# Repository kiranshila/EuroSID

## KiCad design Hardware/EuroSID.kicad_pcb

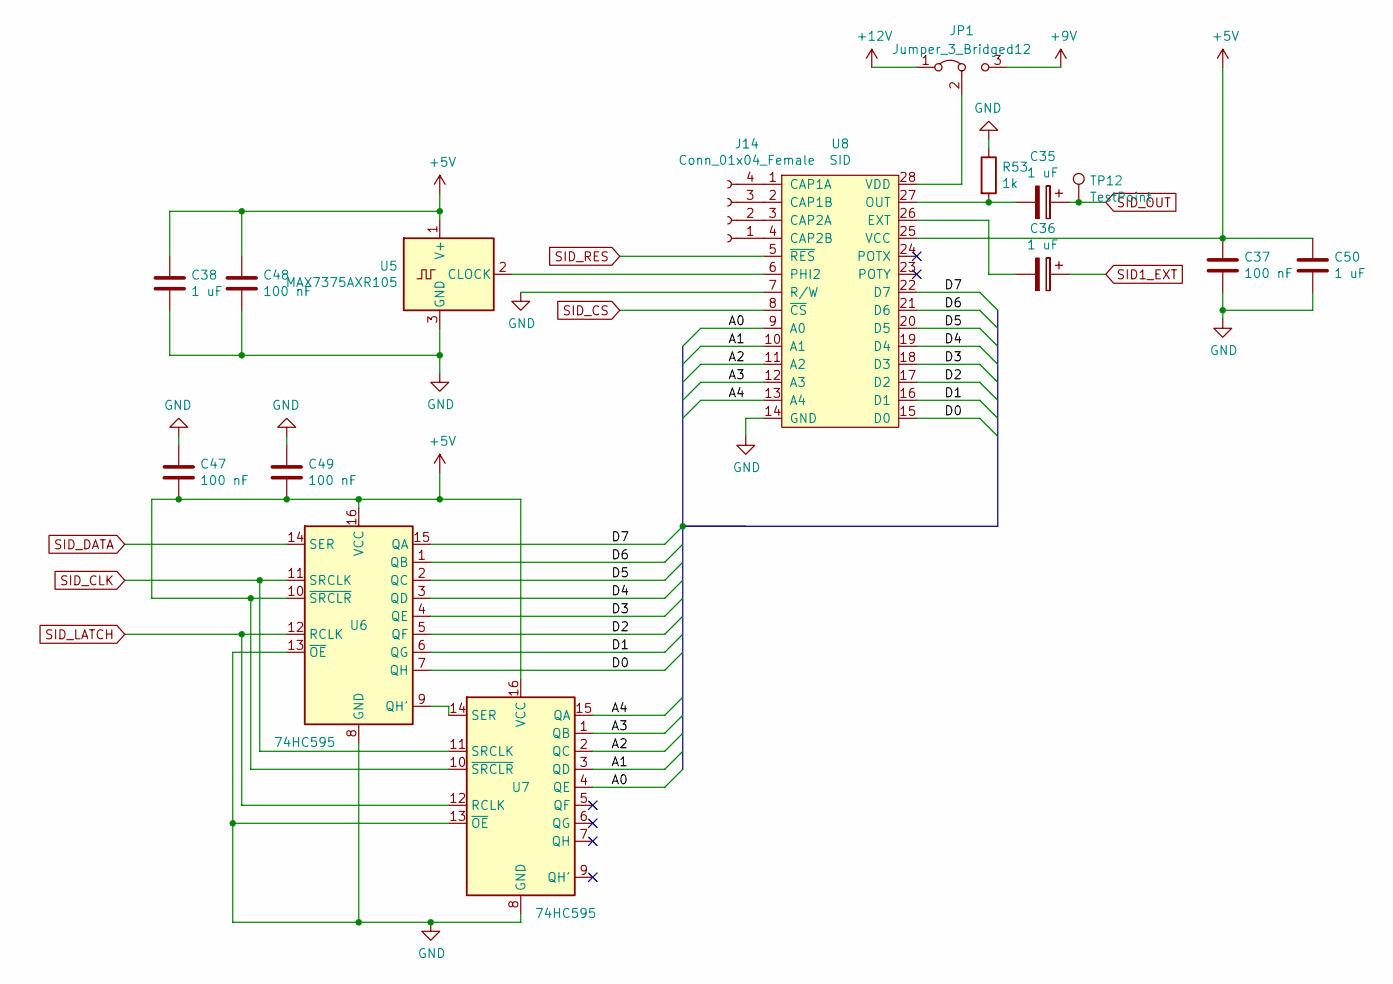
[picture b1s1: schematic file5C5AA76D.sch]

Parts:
C35, C36: 1 uF; CP_EIA-2012-12_Kemet-R
C37, C47, C48, C49: 100 nF; C_0603_1608Metric
C38, C50: 1 uF; C_0603_1608Metric
J14: Conn_01x04_Female; PinSocket_1x04_P2.54mm_Vertical
JP1: Jumper_3_Bridged12; PinHeader_1x03_P2.54mm_Vertical_SMD_Pin1Left
R53: 1k; R_0603_1608Metric
TP12: TestPoint; TestPoint_Pad_D1.0mm
U5: MAX7375AXR105; SOT-323_SC-70
U6, U7: 74HC595; SOIC-16_3.9x9.9mm_P1.27mm
U8: SID; DIP-28_W16.51mm_SMDSocket_LongPads

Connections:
+9V: JP1.3 (B); also elsewhere on the board
+12V: JP1.1 (A); also elsewhere on the board
/SID Chip/A0: U7.4 (QE), U8.9 (A0)
/SID Chip/A1: U7.3 (QD), U8.10 (A1)
/SID Chip/A2: U7.2 (QC), U8.11 (A2)
/SID Chip/A3: U7.1 (QB), U8.12 (A3)
/SID Chip/A4: U7.15 (QA), U8.13 (A4)
/SID Chip/D0: U6.7 (QH), U8.15 (D0)
/SID Chip/D1: U6.6 (QG), U8.16 (D1)
/SID Chip/D2: U6.5 (QF), U8.17 (D2)
/SID Chip/D3: U6.4 (QE), U8.18 (D3)
/SID Chip/D4: U6.3 (QD), U8.19 (D4)
/SID Chip/D5: U6.2 (QC), U8.20 (D5)
/SID Chip/D6: U6.1 (QB), U8.21 (D6)
/SID Chip/D7: U6.15 (QA), U8.22 (D7)
GND: C37.2, C38.2, C47.1, C48.2, C49.1, C50.2, R53.1, U5.3 (GND), U6.8 (GND), U6.13 (~OE), U7.8 (GND), U7.13 (~OE), U8.7 (R/W), U8.14 (GND); also elsewhere on the board
unnamed: C35.2, R53.2, U8.27 (OUT)
unnamed: C36.2, U8.26 (EXT)
unnamed: J14.1, U8.4 (CAP2B)
unnamed: J14.2, U8.3 (CAP2A)
unnamed: J14.3, U8.2 (CAP1B)
unnamed: J14.4, U8.1 (CAP1A)
unnamed: JP1.2 (C), U8.28 (VDD)
unnamed: U5.2 (CLOCK), U8.6 (PHI2)
unnamed: U6.9 (QH'), U7.14 (SER)
SID1_EXT: C36.1; also elsewhere on the board
SID_CLK: U6.11 (SRCLK), U7.11 (SRCLK); also elsewhere on the board
SID_CS: U8.8 (~CS); also elsewhere on the board
SID_DATA: U6.14 (SER); also elsewhere on the board
SID_LATCH: U6.12 (RCLK), U7.12 (RCLK); also elsewhere on the board
SID_OUT: C35.1, TP12.1; also elsewhere on the board
SID_RES: U8.5 (~RES); also elsewhere on the board

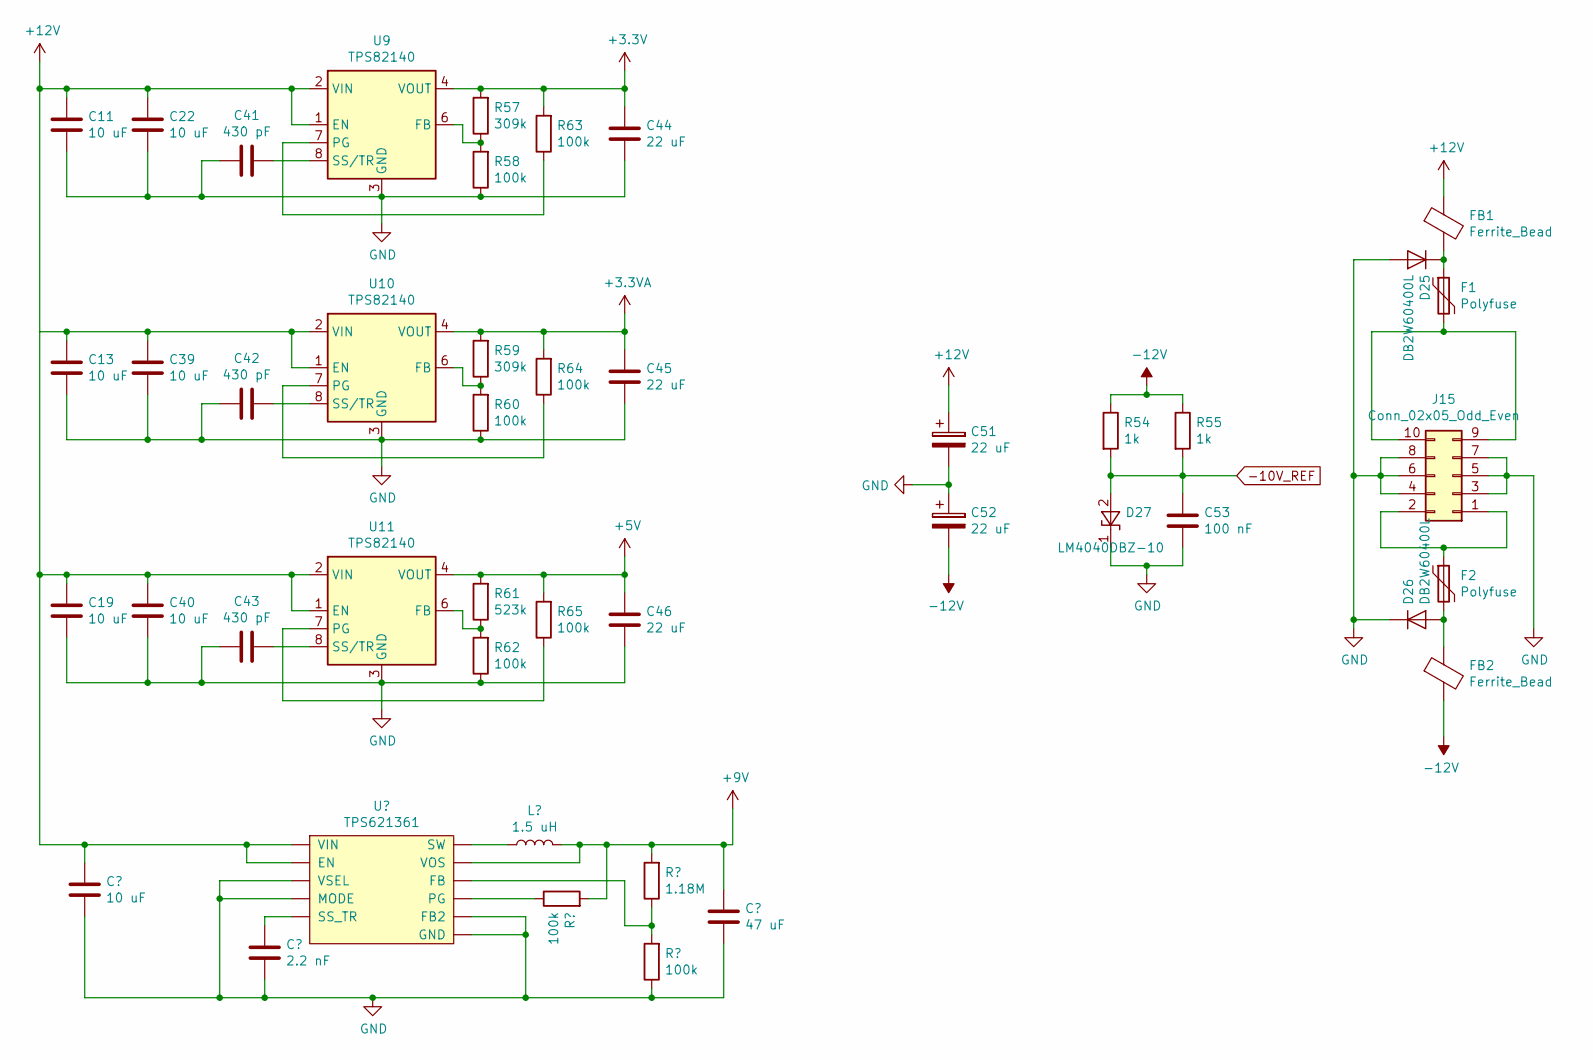
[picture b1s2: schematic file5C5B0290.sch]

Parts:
C11, C13, C19, C22, C39, C40: 10 uF; C_0603_1608Metric
C41, C42, C43: 430 pF; C_0603_1608Metric
C44, C45, C46: 22 uF; C_0603_1608Metric
C51, C52: 22 uF; CP_Elec_4x5.3
C53: 100 nF; C_0603_1608Metric
D25, D26: DB2W60400L; DZ2W160
D27: LM4040DBZ-10; SOT-23
F1, F2: Polyfuse; Fuse_1812_4532Metric
FB1, FB2: Ferrite_Bead; L_0603_1608Metric
J15: Conn_02x05_Odd_Even; IDC-Header_2x05_P2.54mm_Vertical
R54, R55: 1k; R_0603_1608Metric
R57, R59: 309k; R_0603_1608Metric
R58, R60, R62, R63, R64, R65: 100k; R_0603_1608Metric
R61: 523k; R_0603_1608Metric
U9, U10, U11: TPS82140; PSON65P280X300X153-9N

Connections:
+3.3VA: C45.1, R59.2, R64.2, U10.4 (VOUT), U10.5 (VOUT); also elsewhere on the board
+3V3: C44.1, R57.2, R63.2, U9.4 (VOUT), U9.5 (VOUT); also elsewhere on the board
+12V: C11.1, C13.1, C19.1, C22.1, C39.1, C40.1, C51.1, FB1.1, U9.1 (EN), U9.2 (VIN), U10.1 (EN), U10.2 (VIN), U11.1 (EN), U11.2 (VIN); also elsewhere on the board
-10V_REF: C53.1, D27.2 (A), R54.2, R55.2; also elsewhere on the board
-12V: C52.2, FB2.2, R54.1, R55.1; also elsewhere on the board
GND: C11.2, C13.2, C19.2, C22.2, C39.2, C40.2, C41.1, C42.1, C43.1, C44.2, C45.2, C46.2, C51.2, C52.1, C53.2, D25.2 (A), D26.1 (K), D27.1 (K), J15.3, J15.4, J15.5, J15.6, J15.7, J15.8, R58.1, R60.1, R62.1, U9.3 (GND), U9.9 (GND), U10.3 (GND), U10.9 (GND), U11.3 (GND), U11.9 (GND); also elsewhere on the board
unnamed: C41.2, U9.8 (SS/TR)
unnamed: C42.2, U10.8 (SS/TR)
unnamed: C43.2, U11.8 (SS/TR)
unnamed: D25.1 (K), F1.1, FB1.2
unnamed: D26.2 (A), F2.2, FB2.1
unnamed: F1.2, J15.9, J15.10
unnamed: F2.1, J15.1, J15.2
unnamed: R57.1, R58.2, U9.6 (FB)
unnamed: R59.1, R60.2, U10.6 (FB)
unnamed: R61.1, R62.2, U11.6 (FB)
unnamed: R63.1, U9.7 (PG)
unnamed: R64.1, U10.7 (PG)
unnamed: R65.1, U11.7 (PG)

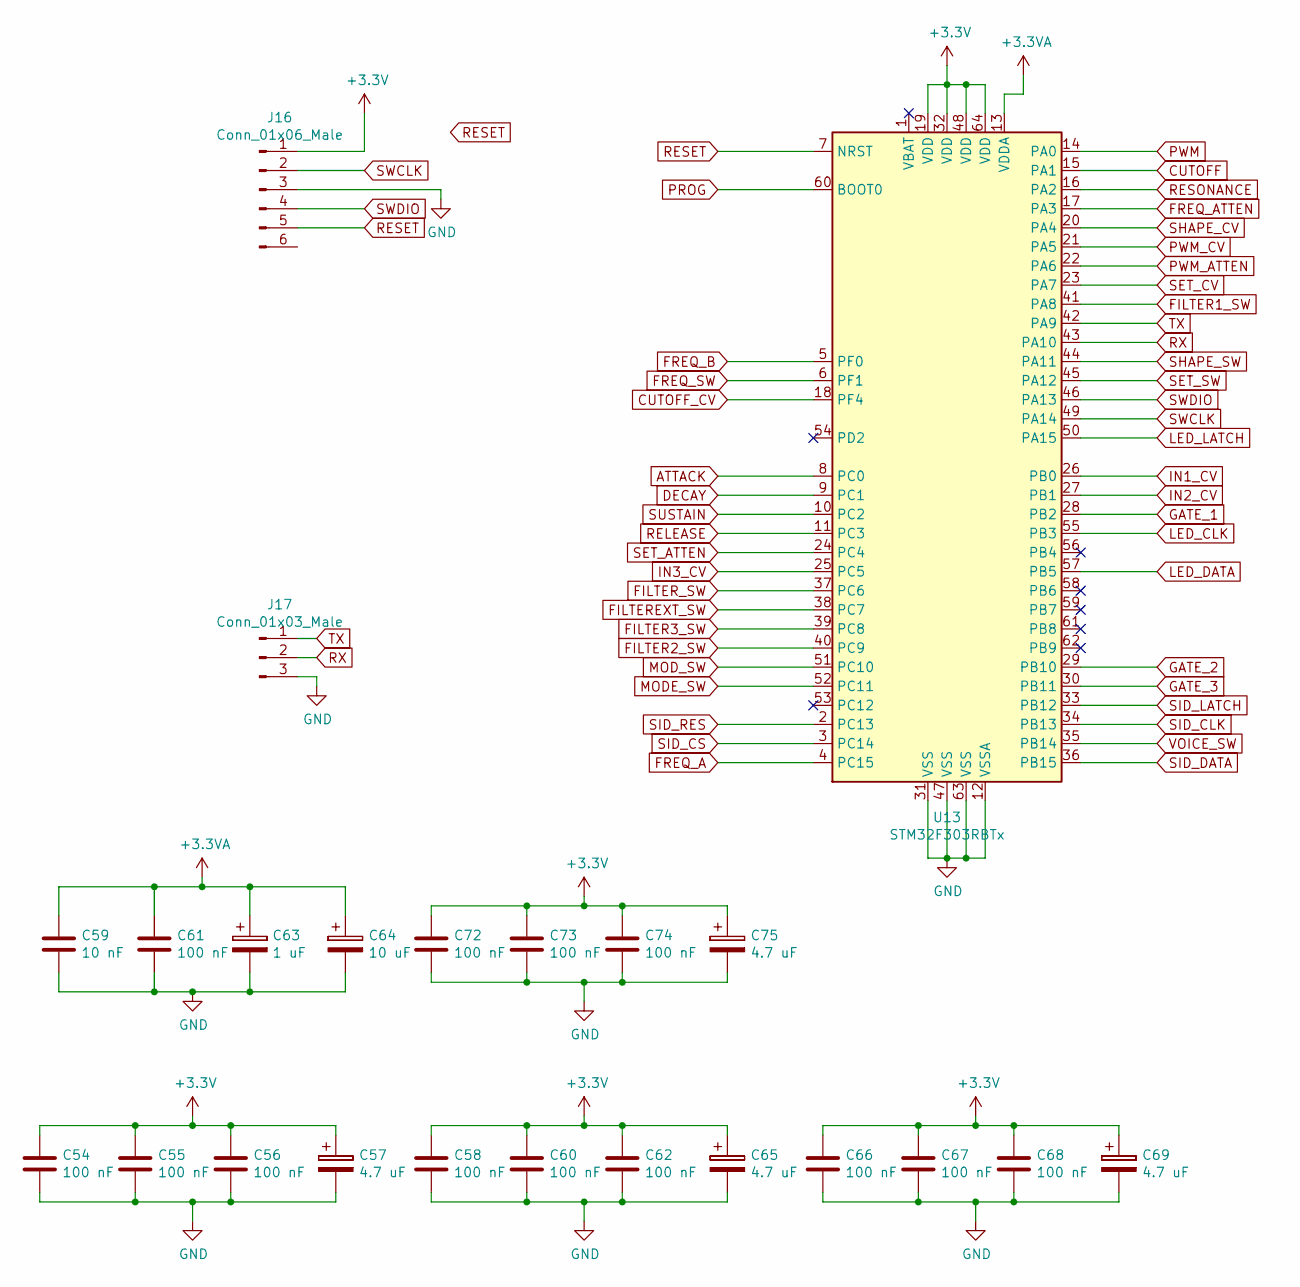
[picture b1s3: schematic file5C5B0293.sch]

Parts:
C54, C55, C56, C58, C60, C61, C62, C66, C67, C68, C72, C73, C74: 100 nF; C_0603_1608Metric
C57, C65, C69, C75: 4.7 uF; CP_EIA-3216-18_Kemet-A
C59: 10 nF; C_0603_1608Metric
C63: 1 uF; CP_EIA-2012-12_Kemet-R
C64: 10 uF; CP_Elec_4x5.7
J16: Conn_01x06_Male; PinSocket_1x06_P2.54mm_Vertical_SMD_Pin1Left
J17: Conn_01x03_Male; PinSocket_1x03_P2.54mm_Vertical_SMD_Pin1Left
U13: STM32F303RBTx; LQFP-64_10x10mm_P0.5mm

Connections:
+3.3VA: C59.1, C61.1, C63.1, C64.1, U13.13 (VDDA); also elsewhere on the board
+3V3: C54.1, C55.1, C56.1, C57.1, C58.1, C60.1, C62.1, C65.1, C66.1, C67.1, C68.1, C69.1, C72.1, C73.1, C74.1, C75.1, J16.1, U13.19 (VDD), U13.32 (VDD), U13.48 (VDD), U13.64 (VDD); also elsewhere on the board
ATTACK: U13.8 (PC0); also elsewhere on the board
CUTOFF: U13.15 (PA1); also elsewhere on the board
CUTOFF_CV: U13.18 (PF4); also elsewhere on the board
DECAY: U13.9 (PC1); also elsewhere on the board
FILTER1_SW: U13.41 (PA8); also elsewhere on the board
FILTER2_SW: U13.40 (PC9); also elsewhere on the board
FILTER3_SW: U13.39 (PC8); also elsewhere on the board
FILTEREXT_SW: U13.38 (PC7); also elsewhere on the board
FILTER_SW: U13.37 (PC6); also elsewhere on the board
FREQ_A: U13.4 (PC15); also elsewhere on the board
FREQ_ATTEN: U13.17 (PA3); also elsewhere on the board
FREQ_B: U13.5 (PF0); also elsewhere on the board
FREQ_SW: U13.6 (PF1); also elsewhere on the board
GATE_1: U13.28 (PB2); also elsewhere on the board
GATE_2: U13.29 (PB10); also elsewhere on the board
GATE_3: U13.30 (PB11); also elsewhere on the board
GND: C54.2, C55.2, C56.2, C57.2, C58.2, C59.2, C60.2, C61.2, C62.2, C63.2, C64.2, C65.2, C66.2, C67.2, C68.2, C69.2, C72.2, C73.2, C74.2, C75.2, J16.3, J17.3, U13.12 (VSSA), U13.31 (VSS), U13.47 (VSS), U13.63 (VSS); also elsewhere on the board
IN1_CV: U13.26 (PB0); also elsewhere on the board
IN2_CV: U13.27 (PB1); also elsewhere on the board
IN3_CV: U13.25 (PC5); also elsewhere on the board
LED_CLK: U13.55 (PB3); also elsewhere on the board
LED_DATA: U13.57 (PB5); also elsewhere on the board
LED_LATCH: U13.50 (PA15); also elsewhere on the board
MODE_SW: U13.52 (PC11); also elsewhere on the board
MOD_SW: U13.51 (PC10); also elsewhere on the board
PROG: U13.60 (BOOT0); also elsewhere on the board
PWM: U13.14 (PA0); also elsewhere on the board
PWM_ATTEN: U13.22 (PA6); also elsewhere on the board
PWM_CV: U13.21 (PA5); also elsewhere on the board
RELEASE: U13.11 (PC3); also elsewhere on the board
RESET: J16.5, U13.7 (NRST); also elsewhere on the board
RESONANCE: U13.16 (PA2); also elsewhere on the board
RX: J17.2, U13.43 (PA10)
SET_ATTEN: U13.24 (PC4); also elsewhere on the board
SET_CV: U13.23 (PA7); also elsewhere on the board
SET_SW: U13.45 (PA12); also elsewhere on the board
SHAPE_CV: U13.20 (PA4); also elsewhere on the board
SHAPE_SW: U13.44 (PA11); also elsewhere on the board
SID_CLK: U13.34 (PB13); also elsewhere on the board
SID_CS: U13.3 (PC14); also elsewhere on the board
SID_DATA: U13.36 (PB15); also elsewhere on the board
SID_LATCH: U13.33 (PB12); also elsewhere on the board
SID_RES: U13.2 (PC13); also elsewhere on the board
SUSTAIN: U13.10 (PC2); also elsewhere on the board
SWCLK: J16.2, U13.49 (PA14)
SWDIO: J16.4, U13.46 (PA13)
TX: J17.1, U13.42 (PA9)
VOICE_SW: U13.35 (PB14); also elsewhere on the board

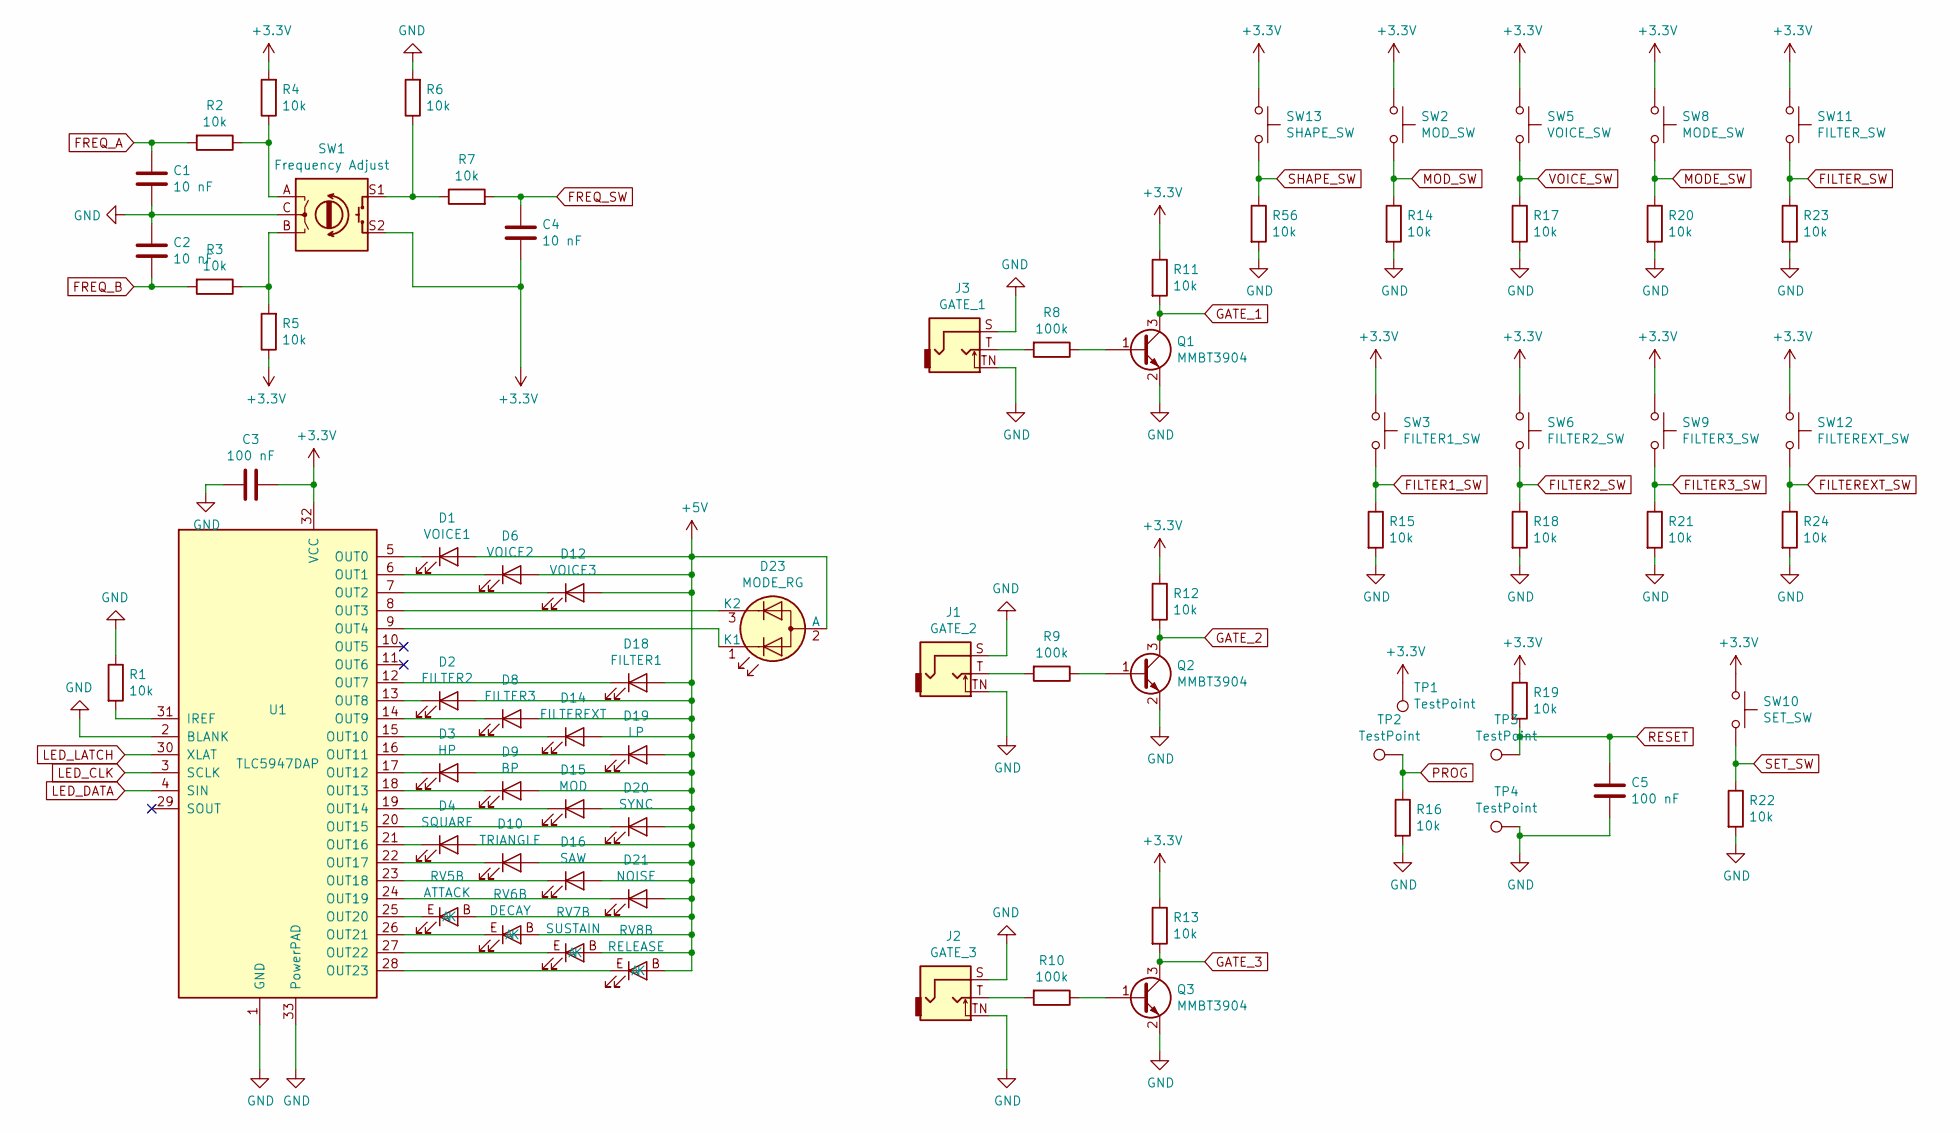
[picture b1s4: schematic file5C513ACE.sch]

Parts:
C1, C2, C4: 10 nF; C_0603_1608Metric
C3, C5: 100 nF; C_0603_1608Metric
D1: VOICE1; LED_0603_1608Metric
D2: FILTER2; LED_0603_1608Metric
D3: HP; LED_0603_1608Metric
D4: SQUARE; LED_0603_1608Metric
D6: VOICE2; LED_0603_1608Metric
D8: FILTER3; LED_0603_1608Metric
D9: BP; LED_0603_1608Metric
D10: TRIANGLE; LED_0603_1608Metric
D12: VOICE3; LED_0603_1608Metric
D14: FILTEREXT; LED_0603_1608Metric
D15: MOD; LED_0603_1608Metric
D16: SAW; LED_0603_1608Metric
D18: FILTER1; LED_0603_1608Metric
D19: LP; LED_0603_1608Metric
D20: SYNC; LED_0603_1608Metric
D21: NOISE; LED_0603_1608Metric
D23: MODE_RG; LED-L1T2_LUMILEDS
J1: GATE_2; Jack_3.5mm_QingPu_WQP-PJ398SM_Vertical_CircularHoles
J2: GATE_3; Jack_3.5mm_QingPu_WQP-PJ398SM_Vertical_CircularHoles
J3: GATE_1; Jack_3.5mm_QingPu_WQP-PJ398SM_Vertical_CircularHoles
Q1, Q2, Q3: MMBT3904; SOT-23
R1, R2, R3, R4, R5, R6, R7, R11, R12, R13, R14, R15, R16, R17, R18, R19, R20, R21, R22, R23, R24, R56: 10k; R_0603_1608Metric
R8, R9, R10: 100k; R_0603_1608Metric
RV5: ATTACK; Potentiometer_Bourns_PTL20_Single_Slide
RV6: DECAY; Potentiometer_Bourns_PTL20_Single_Slide
RV7: SUSTAIN; Potentiometer_Bourns_PTL20_Single_Slide
RV8: RELEASE; Potentiometer_Bourns_PTL20_Single_Slide
SW1: Frequency Adjust; RotaryEncoder_Alps_EC12E-Switch_Vertical_H20mm_CircularMoun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
SW2: MOD_SW; SW_PUSH_6mm_H9.5mm
SW3: FILTER1_SW; SW_PUSH_6mm_H9.5mm
SW5: VOICE_SW; SW_PUSH_6mm_H9.5mm
SW6: FILTER2_SW; SW_PUSH_6mm_H9.5mm
SW8: MODE_SW; SW_PUSH_6mm_H9.5mm
SW9: FILTER3_SW; SW_PUSH_6mm_H9.5mm
SW10: SET_SW; SW_PUSH_6mm_H9.5mm
SW11: FILTER_SW; SW_PUSH_6mm_H9.5mm
SW12: FILTEREXT_SW; SW_PUSH_6mm_H9.5mm
SW13: SHAPE_SW; SW_PUSH_6mm_H9.5mm
TP1, TP2, TP3, TP4: TestPoint; TestPoint_Pad_D1.0mm
U1: TLC5947DAP; HTSSOP-32-1EP_6.1x11mm_P0.65mm_EP5.2x11mm_Mask4.11x4.36mm_T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

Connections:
+3V3: C3.1, C4.2, R4.2, R5.1, R11.1, R12.1, R13.1, R19.1, SW1.S2, SW2.1, SW3.1, SW5.1, SW6.1, SW8.1, SW9.1, SW10.1, SW11.1, SW12.1, SW13.1, TP1.1, U1.32 (VCC); also elsewhere on the board
FILTER1_SW: R15.1, SW3.2; also elsewhere on the board
FILTER2_SW: R18.1, SW6.2; also elsewhere on the board
FILTER3_SW: R21.1, SW9.2; also elsewhere on the board
FILTEREXT_SW: R24.1, SW12.2; also elsewhere on the board
FILTER_SW: R23.1, SW11.2; also elsewhere on the board
FREQ_A: C1.1, R2.2; also elsewhere on the board
FREQ_B: C2.2, R3.2; also elsewhere on the board
FREQ_SW: C4.1, R7.2; also elsewhere on the board
GATE_1: Q1.3 (C), R11.2; also elsewhere on the board
GATE_2: Q2.3 (C), R12.2; also elsewhere on the board
GATE_3: Q3.3 (C), R13.2; also elsewhere on the board
GND: C1.2, C2.1, C3.2, C5.2, J1.S, J1.TN, J2.S, J2.TN, J3.S, J3.TN, Q1.2 (E), Q2.2 (E), Q3.2 (E), R1.1, R6.2, R14.2, R15.2, R16.2, R17.2, R18.2, R20.2, R21.2, R22.2, R23.2, R24.2, R56.2, SW1.C, TP4.1, U1.1 (GND), U1.2 (BLANK), U1.33 (PowerPAD); also elsewhere on the board
LED_CLK: U1.3 (SCLK); also elsewhere on the board
LED_DATA: U1.4 (SIN); also elsewhere on the board
LED_LATCH: U1.30 (XLAT); also elsewhere on the board
MODE_SW: R20.1, SW8.2; also elsewhere on the board
MOD_SW: R14.1, SW2.2; also elsewhere on the board
unnamed: D1.1 (K), U1.5 (OUT0)
unnamed: D2.1 (K), U1.13 (OUT8)
unnamed: D3.1 (K), U1.17 (OUT12)
unnamed: D4.1 (K), U1.21 (OUT16)
unnamed: D6.1 (K), U1.6 (OUT1)
unnamed: D8.1 (K), U1.14 (OUT9)
unnamed: D9.1 (K), U1.18 (OUT13)
unnamed: D10.1 (K), U1.22 (OUT17)
unnamed: D12.1 (K), U1.7 (OUT2)
unnamed: D14.1 (K), U1.15 (OUT10)
unnamed: D15.1 (K), U1.19 (OUT14)
unnamed: D16.1 (K), U1.23 (OUT18)
unnamed: D18.1 (K), U1.12 (OUT7)
unnamed: D19.1 (K), U1.16 (OUT11)
unnamed: D20.1 (K), U1.20 (OUT15)
unnamed: D21.1 (K), U1.24 (OUT19)
unnamed: J1.T, R9.2
unnamed: J2.T, R10.2
unnamed: J3.T, R8.2
unnamed: Q1.1 (B), R8.1
unnamed: Q2.1 (B), R9.1
unnamed: Q3.1 (B), R10.1
unnamed: R1.2, U1.31 (IREF)
unnamed: R2.1, R4.1, SW1.A
unnamed: R3.1, R5.2, SW1.B
unnamed: R6.1, R7.1, SW1.S1
unnamed: RV5.E (K), U1.25 (OUT20)
unnamed: RV6.E (K), U1.26 (OUT21)
unnamed: RV7.E (K), U1.27 (OUT22)
unnamed: RV8.E (K), U1.28 (OUT23)
PROG: R16.1, TP2.1; also elsewhere on the board
RESET: C5.1, R19.2, TP3.1; also elsewhere on the board
SET_SW: R22.1, SW10.2; also elsewhere on the board
SHAPE_SW: R56.1, SW13.2; also elsewhere on the board
VOICE_SW: R17.1, SW5.2; also elsewhere on the board

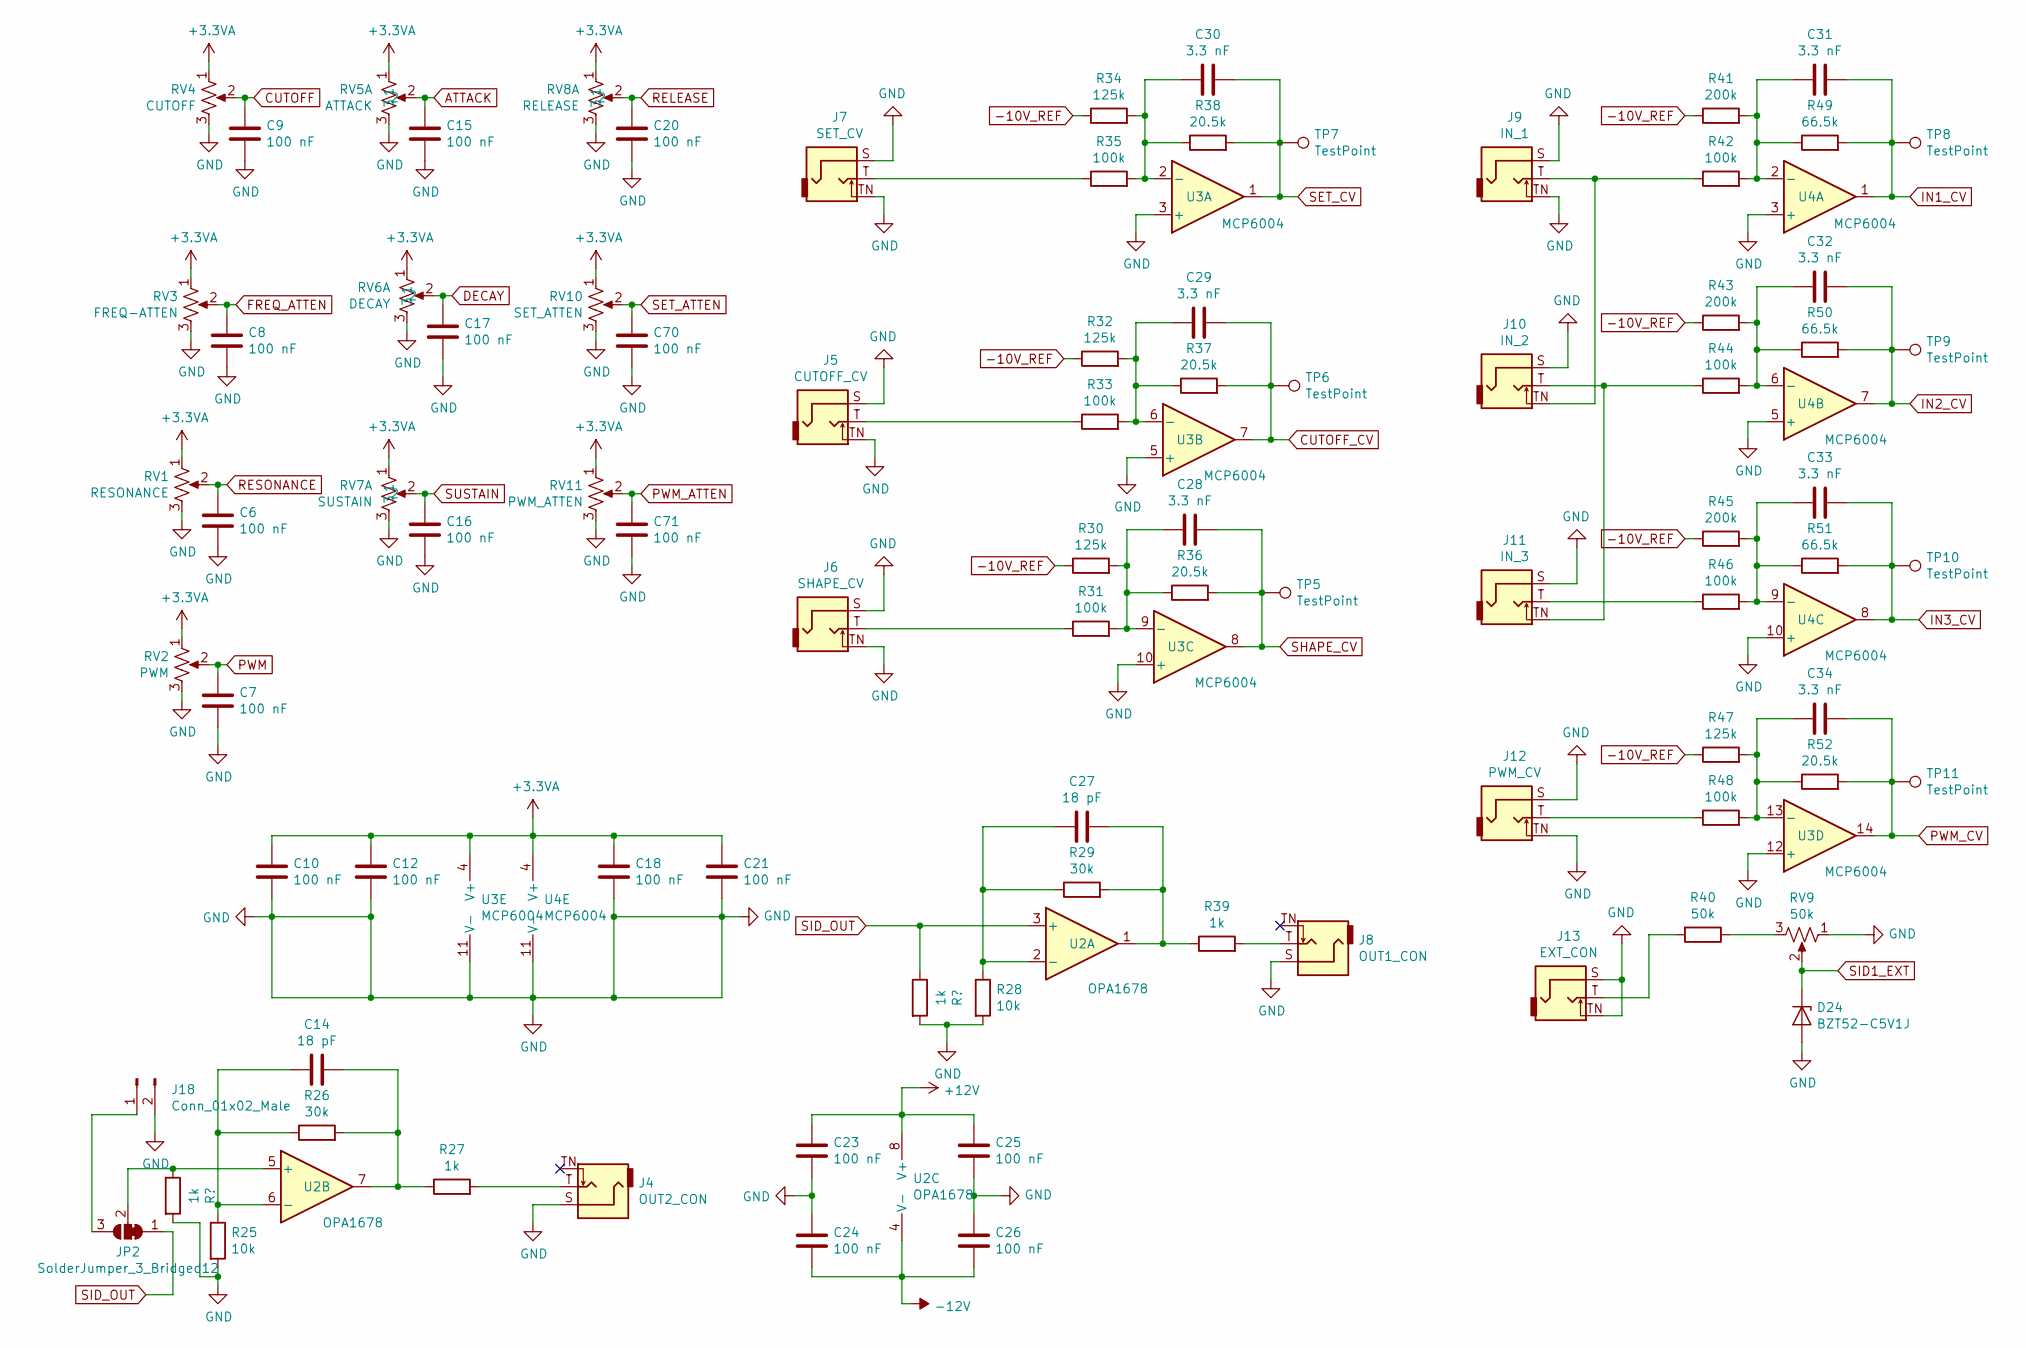
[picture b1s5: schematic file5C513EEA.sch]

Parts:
C6, C7, C8, C9, C10, C12, C15, C16, C17, C18, C20, C21, C23, C24, C25, C26, C70, C71: 100 nF; C_0603_1608Metric
C14, C27: 18 pF; C_0603_1608Metric
C28, C29, C30, C31, C32, C33, C34: 3.3 nF; C_0603_1608Metric
D24: BZT52-C5V1J; D_SOD-123
J4: OUT2_CON; Jack_3.5mm_QingPu_WQP-PJ398SM_Vertical_CircularHoles
J5: CUTOFF_CV; Jack_3.5mm_QingPu_WQP-PJ398SM_Vertical_CircularHoles
J6: SHAPE_CV; Jack_3.5mm_QingPu_WQP-PJ398SM_Vertical_CircularHoles
J7: SET_CV; Jack_3.5mm_QingPu_WQP-PJ398SM_Vertical_CircularHoles
J8: OUT1_CON; Jack_3.5mm_QingPu_WQP-PJ398SM_Vertical_CircularHoles
J9: IN_1; Jack_3.5mm_QingPu_WQP-PJ398SM_Vertical_CircularHoles
J10: IN_2; Jack_3.5mm_QingPu_WQP-PJ398SM_Vertical_CircularHoles
J11: IN_3; Jack_3.5mm_QingPu_WQP-PJ398SM_Vertical_CircularHoles
J12: PWM_CV; Jack_3.5mm_QingPu_WQP-PJ398SM_Vertical_CircularHoles
J13: EXT_CON; Jack_3.5mm_QingPu_WQP-PJ398SM_Vertical_CircularHoles
J18: Conn_01x02_Male; JST_PH_B2B-PH-K_1x02_P2.00mm_Vertical
JP2: SolderJumper_3_Bridged12; SolderJumper-3_P1.3mm_Bridged12_RoundedPad1.0x1.5mm_NumberL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
R25, R28: 10k; R_0603_1608Metric
R26, R29: 30k; R_0603_1608Metric
R27, R39: 1k; R_0603_1608Metric
R30, R32, R34, R47: 125k; R_0603_1608Metric
R31, R33, R35, R42, R44, R46, R48: 100k; R_0603_1608Metric
R36, R37, R38, R52: 20.5k; R_0603_1608Metric
R40: 50k; R_0603_1608Metric
R41, R43, R45: 200k; R_0603_1608Metric
R49, R50, R51: 66.5k; R_0603_1608Metric
RV1: RESONANCE; Potentiometer_Bourns_PTV09A-1_Single_Vertical
RV2: PWM; Potentiometer_Bourns_PTV09A-1_Single_Vertical
RV3: FREQ-ATTEN; Potentiometer_Bourns_PTV09A-1_Single_Vertical
RV4: CUTOFF; Potentiometer_Bourns_PTV09A-1_Single_Vertical
RV5: ATTACK; Potentiometer_Bourns_PTL20_Single_Slide
RV6: DECAY; Potentiometer_Bourns_PTL20_Single_Slide
RV7: SUSTAIN; Potentiometer_Bourns_PTL20_Single_Slide
RV8: RELEASE; Potentiometer_Bourns_PTL20_Single_Slide
RV9: 50k; Potentiometer_Bourns_PTV09A-1_Single_Vertical
RV10: SET_ATTEN; Potentiometer_Bourns_PTV09A-1_Single_Vertical
RV11: PWM_ATTEN; Potentiometer_Bourns_PTV09A-1_Single_Vertical
TP5, TP6, TP7, TP8, TP9, TP10, TP11: TestPoint; TestPoint_Pad_D1.0mm
U2: OPA1678; SOIC-8_3.9x4.9mm_P1.27mm
U3, U4: MCP6004; TSSOP-14_4.4x5mm_P0.65mm

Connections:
+3.3VA: C10.1, C12.1, C18.1, C21.1, RV1.1, RV2.1, RV3.1, RV4.1, RV5.1, RV6.1, RV7.1, RV8.1, RV10.1, RV11.1, U3.4 (V+), U4.4 (V+); also elsewhere on the board
+12V: C23.1, C25.1, U2.8 (V+); also elsewhere on the board
-10V_REF: R30.1, R32.1, R34.1, R41.1, R43.1, R45.1, R47.1; also elsewhere on the board
-12V: C24.2, C26.2, U2.4 (V-); also elsewhere on the board
ATTACK: C15.1, RV5.2; also elsewhere on the board
CUTOFF: C9.1, RV4.2; also elsewhere on the board
CUTOFF_CV: C29.1, R37.2, TP6.1, U3.7; also elsewhere on the board
DECAY: C17.1, RV6.2; also elsewhere on the board
FREQ_ATTEN: C8.1, RV3.2; also elsewhere on the board
GND: C6.2, C7.2, C8.2, C9.2, C10.2, C12.2, C15.2, C16.2, C17.2, C18.2, C20.2, C21.2, C23.2, C24.1, C25.2, C26.1, C70.2, C71.2, D24.2 (A), J4.S, J5.S, J5.TN, J6.S, J6.TN, J7.S, J7.TN, J8.S, J9.S, J9.TN, J10.S, J11.S, J12.S, J12.TN, J13.S, J13.TN, J18.2, R25.2, R28.2, RV1.3, RV2.3, RV3.3, RV4.3, RV5.3, RV6.3, RV7.3, RV8.3, RV9.1, RV10.3, RV11.3, U3.3 (+), U3.5 (+), U3.10 (+), U3.11 (V-), U3.12 (+), U4.3 (+), U4.5 (+), U4.10 (+), U4.11 (V-); also elsewhere on the board
IN1_CV: C31.1, R49.2, TP8.1, U4.1; also elsewhere on the board
IN2_CV: C32.1, R50.2, TP9.1, U4.7; also elsewhere on the board
IN3_CV: C33.1, R51.2, TP10.1, U4.8; also elsewhere on the board
unnamed: C14.1, R26.2, R27.1, U2.7
unnamed: C14.2, R25.1, R26.1, U2.6 (-)
unnamed: C27.1, R29.2, R39.1, U2.1
unnamed: C27.2, R28.1, R29.1, U2.2 (-)
unnamed: C28.2, R30.2, R31.2, R36.1, U3.9 (-)
unnamed: C29.2, R32.2, R33.2, R37.1, U3.6 (-)
unnamed: C30.2, R34.2, R35.2, R38.1, U3.2 (-)
unnamed: C31.2, R41.2, R42.2, R49.1, U4.2 (-)
unnamed: C32.2, R43.2, R44.2, R50.1, U4.6 (-)
unnamed: C33.2, R45.2, R46.2, R51.1, U4.9 (-)
unnamed: C34.2, R47.2, R48.2, R52.1, U3.13 (-)
unnamed: J4.T, R27.2
unnamed: J5.T, R33.1
unnamed: J6.T, R31.1
unnamed: J7.T, R35.1
unnamed: J8.T, R39.2
unnamed: J10.T, J11.TN, R44.1
unnamed: J9.T, J10.TN, R42.1
unnamed: J11.T, R46.1
unnamed: J12.T, R48.1
unnamed: J13.T, R40.2
unnamed: J18.1, JP2.3 (B)
unnamed: JP2.2 (C), U2.5 (+)
unnamed: R40.1, RV9.3
PWM: C7.1, RV2.2; also elsewhere on the board
PWM_ATTEN: C71.1, RV11.2; also elsewhere on the board
PWM_CV: C34.1, R52.2, TP11.1, U3.14; also elsewhere on the board
RELEASE: C20.1, RV8.2; also elsewhere on the board
RESONANCE: C6.1, RV1.2; also elsewhere on the board
SET_ATTEN: C70.1, RV10.2; also elsewhere on the board
SET_CV: C30.1, R38.2, TP7.1, U3.1; also elsewhere on the board
SHAPE_CV: C28.1, R36.2, TP5.1, U3.8; also elsewhere on the board
SID1_EXT: D24.1 (K), RV9.2; also elsewhere on the board
SID_OUT: JP2.1 (A), U2.3 (+); also elsewhere on the board
SUSTAIN: C16.1, RV7.2; also elsewhere on the board

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

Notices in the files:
parts and their libraries:
Copyright 2016 Accelerated Designs. All rights reserved.
